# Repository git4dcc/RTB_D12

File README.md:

# RTB_D12

My Homebrew [D12](https://rtb4dcc.de/hardware/decoder/d12/) decoder is a drop in replacement for the original analog FLM (#7230) PCB. The decoder is designed to integrate into the [RTB](https://rtb4dcc.de/concept/) digital control infrastructure.

<details>
<summary>See also</summary>

- [RTB_D13 - custom](/../../../../git4dcc/RTB_D13) (Minitrix coach)
- [RTB_D15 - custom](/../../../../git4dcc/RTB_D15) (Minitrix V160)
- [RTB_D16 - NEM651](/../../../../git4dcc/RTB_D16)
- [RTB_D20 - NEM651](/../../../../git4dcc/RTB_D20)
- [RTB_D21 - Next18](/../../../../git4dcc/RTB_D21)
- [RTB_D22 - Plux16](/../../../../git4dcc/RTB_D22)
- [RTB_D23 - NEM652](/../../../../git4dcc/RTB_D23)

</details>

<details>
<summary>User Guides</summary>

- User Guide - DE
- [User Guide - EN](https://rtb4dcc.de/rtb_decoder_reference_en/)

</details>

<br>

## Decoder features
- **Fleischmann V100** PCB decoder
- **DCC**
  - DCC-A automatic logon
  - DCC-R protocol extension
  - Service Mode Programming
- **Railcom**
  - Channel 1/2
  - POM, xPOM
  - DYN: Speed, QoS, Track-voltage, Motor-current, AUX-current, Temp, Distance travelled
- 7-18V track voltage
- heartbeat LED
- adjustable max motor current (default 250mA)
- adjustable max AUX current (default 250mA)
- over temp protection
- Function output: LF/LR (dimmable, 1.4kHz), LED on PCB
- Function output: AUX1/AUX2 (dimmable, 1.4kHz) logic level (3.3V)
- Function output: AUX3/AUX4 open drain
- Function output: AUX5 cabin light, LED on PCB
- buffer capacitor 2x330uF
- <10mA idle power consumption
- Firmware update over main tracks via DCC-R protocol

# Hardware
The current PCB layout uses SMD footprints with 0.5mm pitch and mainly 0603 parts. Reflow soldering is recommended whereas handsoldering will be difficult.

## PCB
- 4-layer PCB, FR4, 0.8mm
- CPU: AVR64DA32
- Motor bridge: DRV8231
- Inrush limiter: R/D combination

## Kicad
[Schematic](doc/D12_schematic.pdf) | [Layout](doc/D12_layout.pdf)

The BOM is tailored to JLCPCB part#.

<details>
<summary>Dependency</summary>
<br>

:yellow_circle: Requires my Kicad project library [RTB_SamacSys](https://github.com/git4dcc/RTB_SamacSys) in the same directory tree.

</details>

## Firmware
Filename structure: { **pcb** }{ **code** }{ **version** }.hex

Example: **D12F0001**.hex

|   | Description |
| --- | --- |
| **pcb** | Name of matching hardware (**D12**) |
| **code** | Type of code contained (**R**=rom, **B**=bootloader, **F**=flash, **U**=bld update, **P**=UPDI factory code) |
| **version** | Release version (**####**) |

[Firmware files](firmware)

# Images

# YouTube
See the D12 decoder in action.<br><br>

This project is intended for hobby use only and is distributed in accordance with the Apache License 2.0 agreement.

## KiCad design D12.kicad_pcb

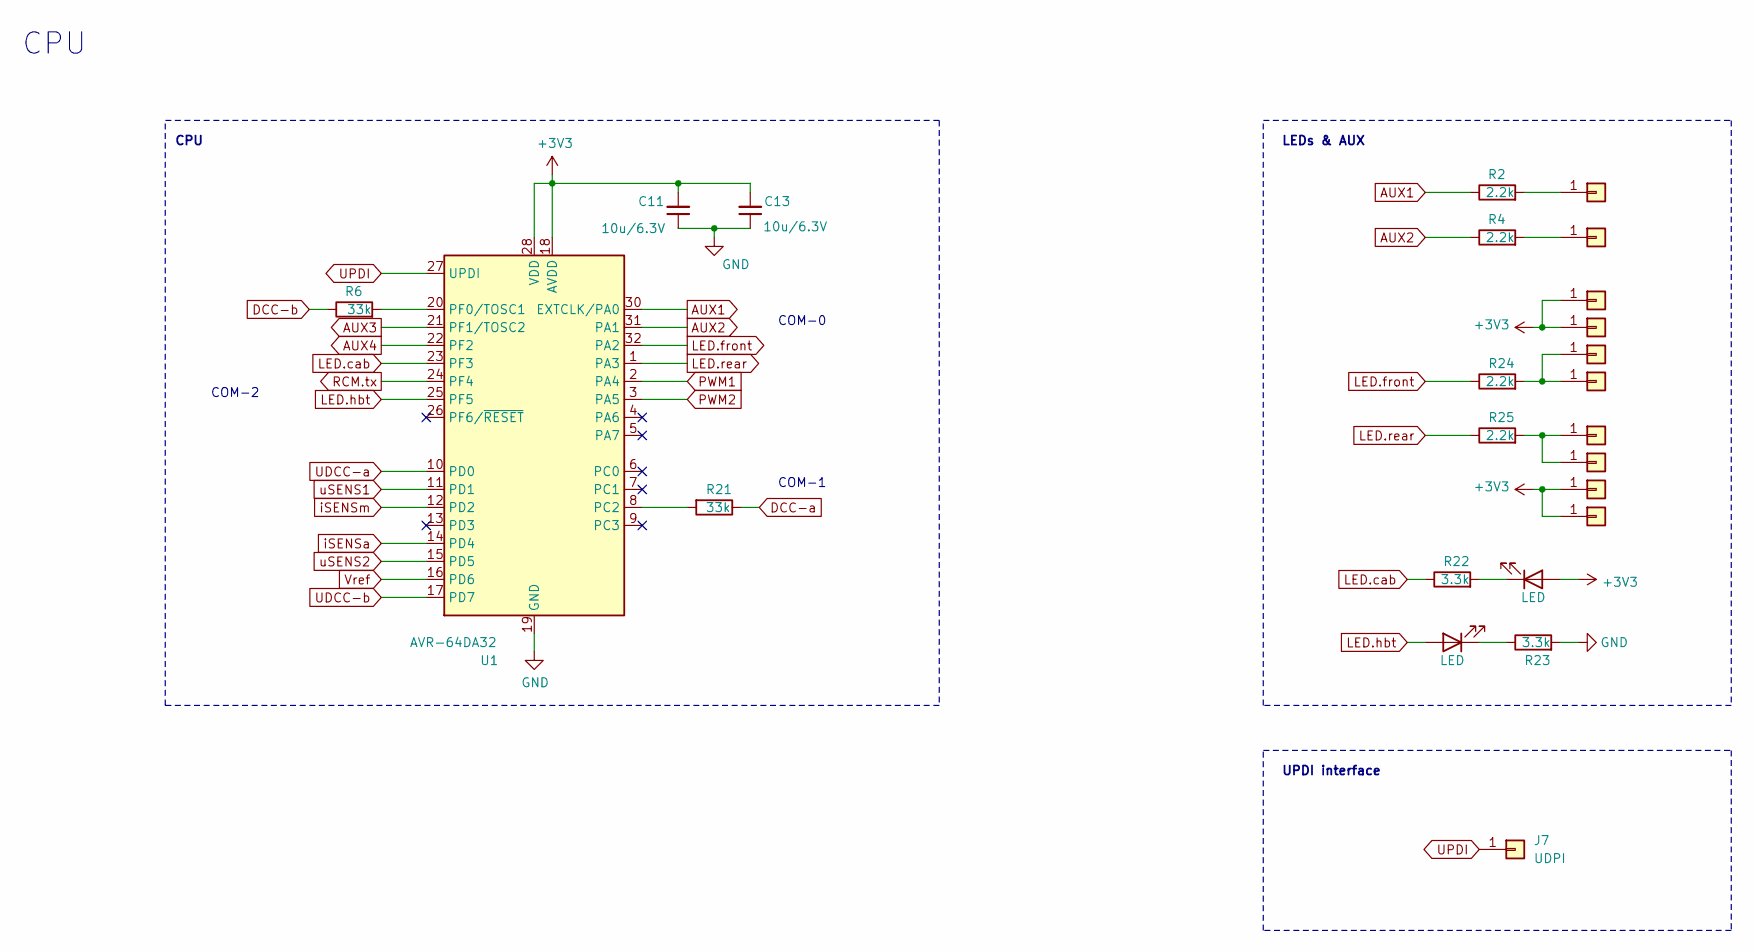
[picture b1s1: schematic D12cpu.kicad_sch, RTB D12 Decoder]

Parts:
C11, C13: 10u/6.3V; C_0402_1005Metric; LCSC Part # C15525
D3: LED; LED_0402_1005Metric; LCSC Part # C74342
D5: LED; LED_0402_1005Metric; LCSC Part # C130724
J1, J5, J8, J9, J20, J21: Conn_01x01; TestPoint_Pad_1.0x1.0mm
J7: UDPI; Solder 0.8 x 0.8
J16: Aux1; Solder 0.8 x 0.8
J17: Aux2; Solder 0.8 x 0.8
J18, J19: Conn_01x01; Solder 0.8 x 0.8
R2, R4, R24, R25: 2.2k; R_0402_1005Metric; LCSC Part # C25879
R6, R21: 33k; R_0402_1005Metric; LCSC Part # C25779
R22, R23: 3.3k; R_0402_1005Metric; LCSC Part # C25890
U1: AVR-64DA32; VQFN-32-1EP_5x5mm_P0.5mm_EP3.1x3.1mm; LCSC Part # C3225673

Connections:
+3V3: C11.2, C13.2, D3.2 (A), J8.1 (Pin_1_1), J9.1 (Pin_1_1), J20.1 (Pin_1_1), J21.1 (Pin_1_1), U1.18 (AVDD), U1.28 (VDD); also elsewhere on the board
AUX1: R2.1, U1.30 (EXTCLK/PA0)
AUX2: R4.1, U1.31 (PA1)
AUX3: U1.21 (PF1/TOSC2); also elsewhere on the board
AUX4: U1.22 (PF2); also elsewhere on the board
DCC-a: R21.1; also elsewhere on the board
DCC-b: R6.1; also elsewhere on the board
GND: C11.1, C13.1, R23.2, U1.19 (GND), U1.29 (GND), U1.33 (GND); also elsewhere on the board
LED.cab: R22.1, U1.23 (PF3)
LED.front: R24.1, U1.32 (PA2)
LED.hbt: D5.2 (A), U1.25 (PF5)
LED.rear: R25.1, U1.1 (PA3)
unnamed: D3.1 (K), R22.2
unnamed: D5.1 (K), R23.1
unnamed: J1.1 (Pin_1_1), J18.1 (Pin_1_1), R24.2
unnamed: J16.1 (Pin_1_1), R2.2
unnamed: J17.1 (Pin_1_1), R4.2
unnamed: J5.1 (Pin_1_1), J19.1 (Pin_1_1), R25.2
unnamed: R21.2, U1.8 (PC2)
unnamed: R6.2, U1.20 (PF0/TOSC1)
PWM1: U1.2 (PA4); also elsewhere on the board
PWM2: U1.3 (PA5); also elsewhere on the board
RCM.tx: U1.24 (PF4); also elsewhere on the board
UDCC-a: U1.10 (PD0); also elsewhere on the board
UDCC-b: U1.17 (PD7); also elsewhere on the board
UPDI: J7.1 (Pin_1_1), U1.27 (UPDI)
Vref: U1.16 (PD6); also elsewhere on the board
iSENSa: U1.14 (PD4); also elsewhere on the board
iSENSm: U1.12 (PD2); also elsewhere on the board
uSENS1: U1.11 (PD1); also elsewhere on the board
uSENS2: U1.15 (PD5); also elsewhere on the board

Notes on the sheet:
UPDI interface
COM-1
COM-2
CPU
LEDs & AUX
COM-0

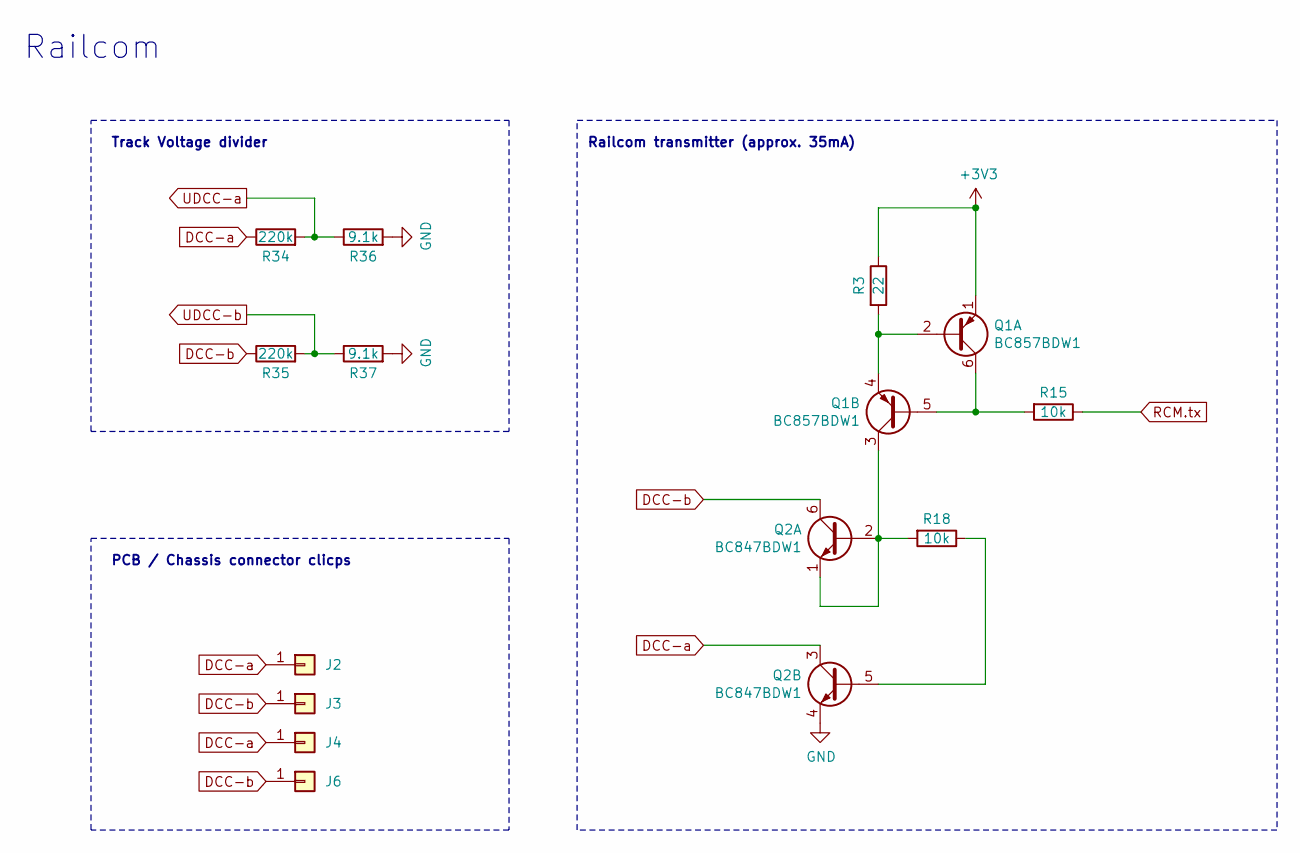
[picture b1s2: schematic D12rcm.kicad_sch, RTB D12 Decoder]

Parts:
J2, J3, J4, J6: Conn_01x01; TestPoint_THTPad_1.5x1.5mm_Drill0.7mm
Q1: BC857BDW1; SOT-666; LCSC Part # C282521
Q2: BC847BDW1; SOT-666; LCSC Part # C455062
R3: 22; R_0402_1005Metric; LCSC Part # C25092
R15, R18: 10k; R_0402_1005Metric; LCSC Part # C25744
R34, R35: 220k; R_0402_1005Metric; LCSC Part # C25767
R36, R37: 9.1k; R_0402_1005Metric; LCSC Part # C25926

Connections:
+3V3: Q1.1 (E1), R3.1; also elsewhere on the board
DCC-a: J2.1 (Pin_1_1), J4.1 (Pin_1_1), Q2.3 (C2), R34.1; also elsewhere on the board
DCC-b: J3.1 (Pin_1_1), J6.1 (Pin_1_1), Q2.6 (C1), R35.1; also elsewhere on the board
GND: Q2.4 (E2), R36.2, R37.2; also elsewhere on the board
unnamed: Q1.2 (B1), Q1.4 (E2), R3.2
unnamed: Q1.5 (B2), Q1.6 (C1), R15.2
unnamed: Q1.3 (C2), Q2.1 (E1), Q2.2 (B1), R18.2
unnamed: Q2.5 (B2), R18.1
RCM.tx: R15.1; also elsewhere on the board
UDCC-a: R34.2, R36.1; also elsewhere on the board
UDCC-b: R35.2, R37.1; also elsewhere on the board

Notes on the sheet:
PCB / Chassis connector clicps
Railcom transmitter (approx. 35mA)
Railcom
Track Voltage divider

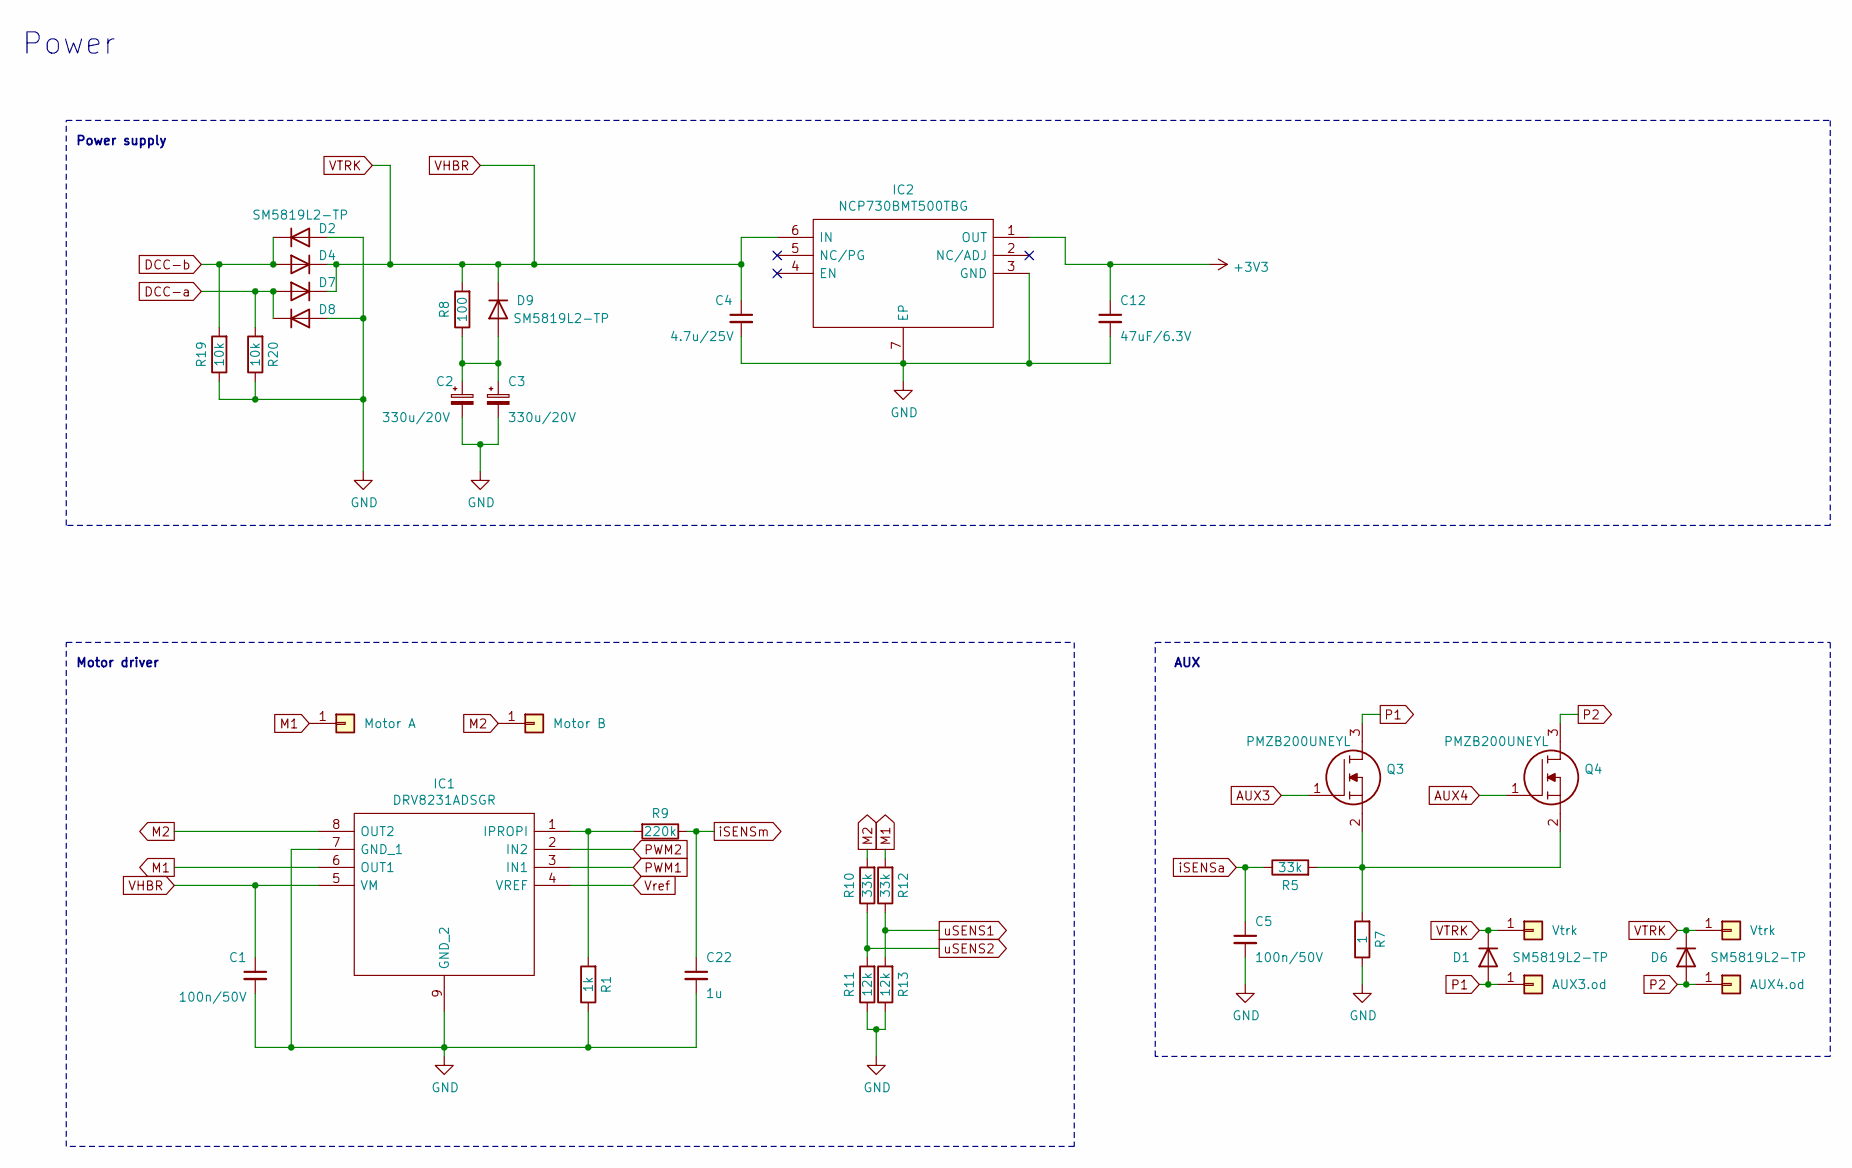
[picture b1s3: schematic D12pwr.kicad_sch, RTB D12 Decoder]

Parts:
C1, C5: 100n/50V; C_0402_1005Metric; LCSC Part # C307331
C2, C3: 330u/20V; CP_EIA-7361-38_AVX-V
C4: 4.7u/25V; C_0402_1005Metric; LCSC Part # C2858031
C12: 47uF/6.3V; C_0805_2012Metric; LCSC Part # C16780
C22: 1u; C_0402_1005Metric; LCSC Part # C52923
D1, D2, D4, D6, D7, D8, D9: SM5819L2-TP; SM5819L2TP; LCSC Part # C6297199
IC1: DRV8231ADSGR; SON50P200X200X80-9N; LCSC Part # C5139865
IC2: NCP730BMT500TBG; WSON-6-1EP_2x2mm_P0.65mm_EP1x1.6mm_ThermalVias; LCSC Part # C892822
J10: Motor A; Solder 2.0 x 0.8
J11: Motor B; Solder 2.0 x 0.8
J12, J14: Vtrk; Solder 0.8 x 0.8
J13: AUX4.od; Solder 0.8 x 0.8
J15: AUX3.od; Solder 0.8 x 0.8
Q3, Q4: PMZB200UNEYL; LCSC Part # C547292
R1: 1k; R_0402_1005Metric; LCSC Part # C11702
R5, R10, R12: 33k; R_0402_1005Metric; LCSC Part # C25779
R7: 1; R_0603_1608Metric; LCSC Part # C22936
R8: 100; R_0402_1005Metric; LCSC Part # C25076
R9: 220k; R_0402_1005Metric; LCSC Part # C25767
R11, R13: 12k; R_0402_1005Metric; LCSC Part # C25752
R19, R20: 10k; R_0402_1005Metric; LCSC Part # C25744

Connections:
+3V3: C12.1, IC2.1 (OUT); also elsewhere on the board
AUX3: Q3.1; also elsewhere on the board
AUX4: Q4.1; also elsewhere on the board
DCC-a: D7.2 (A), D8.1 (K), R20.2; also elsewhere on the board
DCC-b: D2.1 (K), D4.2 (A), R19.2; also elsewhere on the board
GND: C1.2, C2.2, C3.2, C4.2, C5.2, C12.2, C22.2, D2.2 (A), D8.2 (A), IC1.7 (GND_1), IC1.9 (GND_2), IC2.3 (GND), IC2.7 (EP), R1.1, R7.1, R11.1, R13.1, R19.1, R20.1; also elsewhere on the board
M1: IC1.6 (OUT1), J10.1 (Pin_1_1), R12.2
M2: IC1.8 (OUT2), J11.1 (Pin_1_1), R10.2
unnamed: C2.1, C3.1, D9.2 (A), R8.1
unnamed: IC1.1 (IPROPI), R1.2, R9.2
unnamed: Q3.2, Q4.2, R5.2, R7.2
P1: D1.2 (A), J15.1 (Pin_1_1), Q3.3
P2: D6.2 (A), J13.1 (Pin_1_1), Q4.3
PWM1: IC1.3 (IN1); also elsewhere on the board
PWM2: IC1.2 (IN2); also elsewhere on the board
VHBR: C1.1, C4.1, D1.1 (K), D4.1 (K), D6.1 (K), D7.1 (K), D9.1 (K), IC1.5 (VM), IC2.6 (IN), J12.1 (Pin_1_1), J14.1 (Pin_1_1), R8.2
Vref: IC1.4 (VREF); also elsewhere on the board
iSENSa: C5.1, R5.1; also elsewhere on the board
iSENSm: C22.1, R9.1; also elsewhere on the board
uSENS1: R12.1, R13.2; also elsewhere on the board
uSENS2: R10.1, R11.2; also elsewhere on the board

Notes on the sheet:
Power supply
Motor driver
AUX
Power

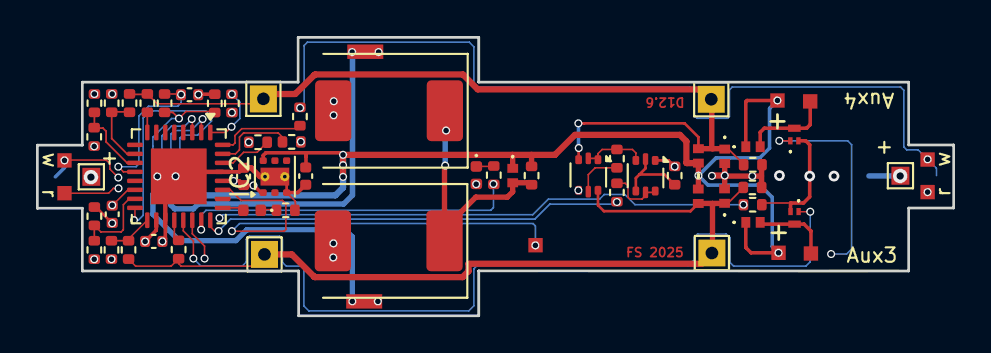
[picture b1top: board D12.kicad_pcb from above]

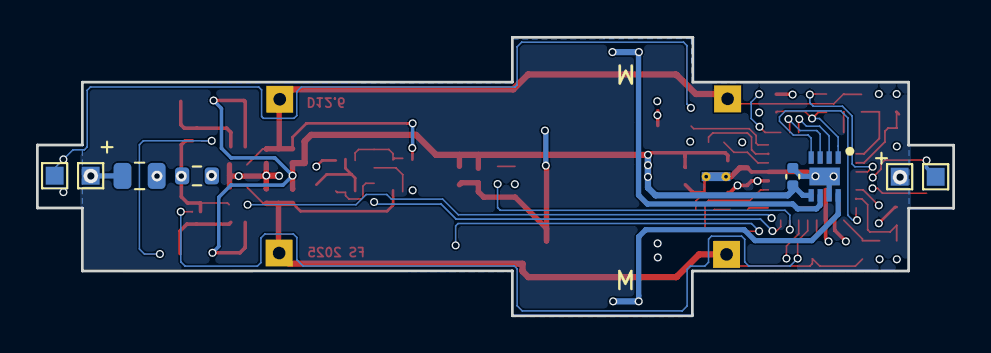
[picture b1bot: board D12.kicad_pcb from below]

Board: 4 copper layers, 50.9 x 15.5 mm, 72 parts (8 on the bottom side), 43 nets.

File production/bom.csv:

Designator,Footprint,Quantity,Value,LCSC Part #
C1,0402,1,100n/50V,C307331
"C11, C13",0402,2,10u/6.3V,C15525
C12,0805,1,47uF/6.3V,C16780
"C2, C3",CP_EIA-7361-38_AVX-V,2,330u/20V,
C22,0402,1,1u,C52923
C4,0402,1,4.7u/25V,C2858031
C5,0402,1,100n,C307331
"D1, D2, D4, D6, D7, D8, D9",SM5819L2TP,7,SM5819L2-TP,C6297199
D3,0402,1,LED,C74342 
D5,0402,1,LED,C130724
IC1,SON50P200X200X80-9N,1,DRV8231ADSGR,C5139865
IC2,WSON-6-1EP_2x2mm_P0.65mm_EP1x1.6mm_ThermalVias,1,NCP730BMT500TBG,C892822
"J1, J20, J21, J5, J8, J9",TestPoint_Pad_1.0x1.0mm,6,Conn_01x01,
J10,Solder 2.0 x 0.8,1,Motor A,
J11,Solder 2.0 x 0.8,1,Motor B,
"J12, J14",Solder 0.8 x 0.8,2,Vtrk,
J13,Solder 0.8 x 0.8,1,AUX4.od,
J15,Solder 0.8 x 0.8,1,AUX3.od,
J16,Solder 0.8 x 0.8,1,Aux1,
J17,Solder 0.8 x 0.8,1,Aux2,
"J18, J19",Solder 0.8 x 0.8,2,Conn_01x01,
"J2, J3, J4, J6",TestPoint_THTPad_1.5x1.5mm_Drill0.7mm,4,Conn_01x01,
J7,Solder 0.8 x 0.8,1,UDPI,
Q1,SOT-666,1,BC857BDW1,C282521
Q2,SOT-666,1,BC847BDW1,C455062
"Q3, Q4",PMZB200UNEYL,2,PMZB200UNEYL,C547292
R1,0402,1,1k,C11702
"R10, R12, R21, R5, R6",0402,5,33k,C25779
"R11, R13",0402,2,12k,C25752
"R15, R18, R19, R20",0402,4,10k,C25744
"R2, R24, R25, R4",0402,4,2.2k,C25879
"R22, R23",0402,2,3.3k,C25890
R3,0402,1,22,C25092
"R34, R35, R9",0402,3,220k,C25767
"R36, R37",0402,2,9.1k,C25926
R7,0603,1,1,C22936
R8,0402,1,68,C25076
U1,VQFN-32-1EP_5x5mm_P0.5mm_EP3.1x3.1mm,1,AVR-64DA32,C3225673

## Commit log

2024-12-08 initial
2025-03-22 add: decoder lock
2025-08-05 mod: led automation
2026-02-20 git mirror test
2026-06-29 migrated to Kicad 10

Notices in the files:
D12.kicad_pcb:
Licensed under the Apache License, Version 2
